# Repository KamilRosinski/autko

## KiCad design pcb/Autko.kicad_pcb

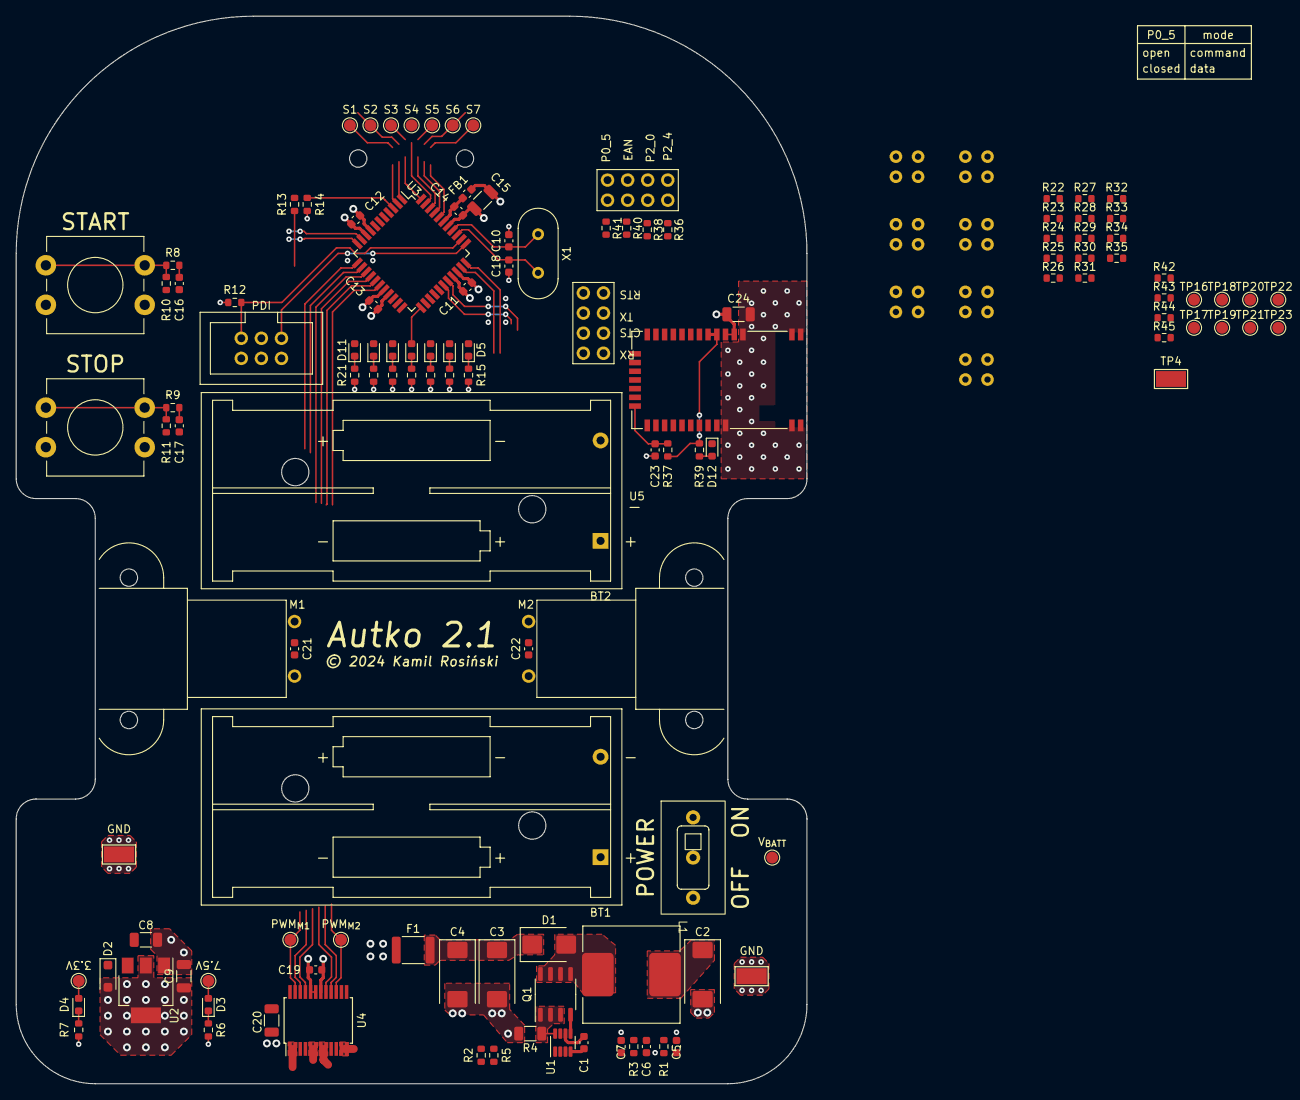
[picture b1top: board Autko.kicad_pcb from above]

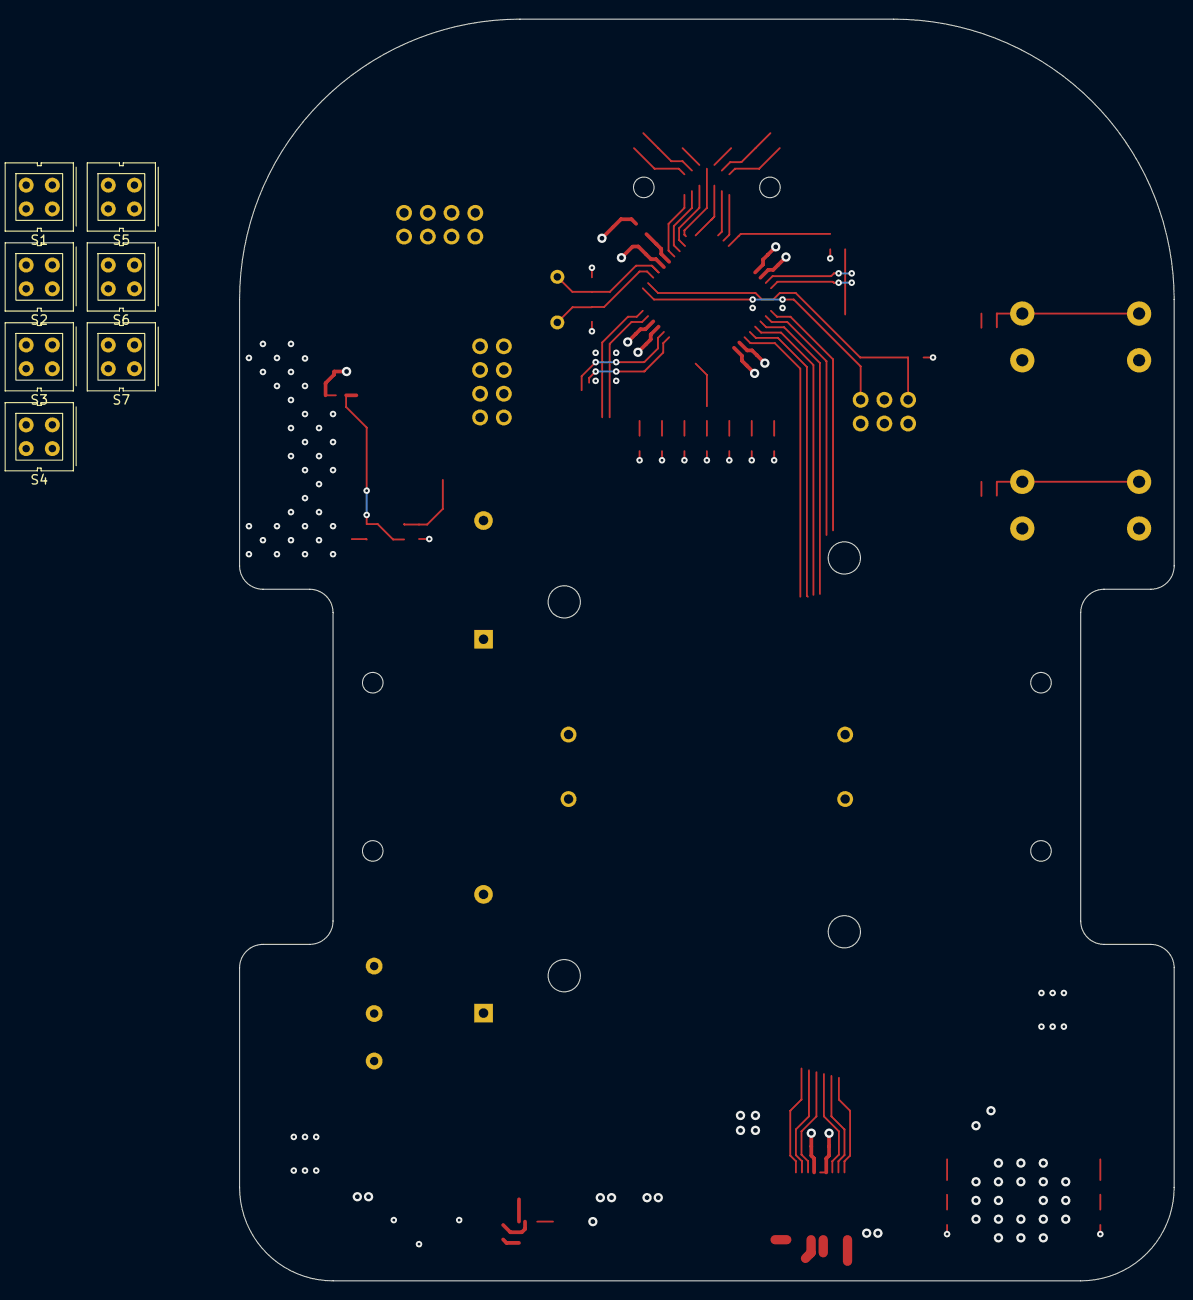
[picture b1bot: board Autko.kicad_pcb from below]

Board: 4 copper layers, 100.0 x 135.0 mm, 131 parts (7 on the bottom side), 88 nets.

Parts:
BT1, BT2: 2xAAA; BatteryHolder_Keystone_2468_2xAAA
C1, C5, C11, C12, C13, C14, C16, C17, C19, C21, C22, C23: 100nF; C_0603_1608Metric
C2: 47uF; CP_EIA-7343-20_Kemet-V
C3, C4: 33uF; CP_EIA-7343-20_Kemet-V
C6: 2.2nF; C_0603_1608Metric
C7: 100pF; C_0603_1608Metric
C8: 1uF; C_1206_3216Metric
C9, C15, C20, C24: 10uF; C_1206_3216Metric
C10, C18: 30pF; C_0603_1608Metric
D1: SL52-3G; D_SMB
D2: SL1A; D_SOD-123F
D3, D4: GREEN; LED_0603_1608Metric
D5, D6, D7, D8, D9, D10, D11: ORANGE; LED_0603_1608Metric
D12: BLUE; LED_0603_1608Metric
F1: 2A; Fuse_1812_4532Metric
FB1: 220R; C_0603_1608Metric
J1: PDI; IDC-Header_2x03_P2.54mm_Vertical
JP1, JP2: Jumper_x4_Bridged; PinHeader_2x04_P2.54mm_Vertical
L1: 3.3uH; Coilcraft_MSS1260
M1: LEFT; Pololu_DC_micro
M2: RIGHT; Pololu_DC_micro
Q1: SO-8_3.9x4.9mm_P1.27mm
R1: 1MR; R_0603_1608Metric
R2: 53.6kR; R_0603_1608Metric
R3: 18kR; R_0603_1608Metric
R4: 20mR; R_1206_3216Metric
R5: 10.2kR; R_0603_1608Metric
R6: 5.1kR; R_0603_1608Metric
R7: 820R; R_0603_1608Metric
R8, R9, R12, R13, R14, R37: 10kR; R_0603_1608Metric
R10, R11, R42, R43, R44, R45: 1kR; R_0603_1608Metric
R15, R16, R17, R18, R19, R20, R21: 680R; R_0603_1608Metric
R22, R24, R26, R28, R30, R32, R34: 640R; R_0603_1608Metric
R23, R25, R27, R29, R31, R33, R35: 20kR; R_0603_1608Metric
R36, R38, R39, R40, R41: 100R; R_0603_1608Metric
S1, S2, S3, S4, S5, S6, S7: CNY70; Vishay_CNY70
SW1: POWER; Knitter-Switch_MSS_3112_D
SW2: START; 12mm_tact_switch
SW3: STOP; 12mm_tact_switch
TP1, TP2, TP6, TP7, TP8, TP9, TP10, TP11, TP12, TP13, TP14, TP15, TP16, TP17, TP18, TP19, TP20, TP21, TP22, TP23: TestPoint; TestPoint_Pad_D1.5mm
TP3, TP4, TP5: TestPoint; TestPoint_Keystone_5019_Minature
U1: LTC3872; SOT-23-8
U2: TLV761; SOT-223-3_TabPin2
U3: ATxmega16A4U-A; TQFP-44_10x10mm_P0.8mm
U4: TB6612FNG; SSOP-24_5.3x8.2mm_P0.65mm
U5: RN4678
X1: 8MHz; Crystal_HC49-4H_Vertical

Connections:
+3.3V: C9.1, C11.1, C12.1, C13.1, C15.1, C19.1, C24.1, D2.2 (A), D4.2 (A), FB1.2, J1.2, R12.1, S1.3 (C), S2.3 (C), S3.3 (C), S4.3 (C), S5.3 (C), S6.3 (C), S7.3 (C), SW2.2, SW3.2, TP6.1, U2.2 (VO), U3.9 (VCC), U3.19 (VCC), U3.31 (VCC), U4.19 (STBY), U4.20 (VCC), U5.4 (BAT_IN), U5.5 (SW_BTN)
+7.5V: C8.1, C20.1, D2.1 (K), D3.2 (A), F1.2, S1.1 (A), S2.1 (A), S3.1 (A), S4.1 (A), S5.1 (A), S6.1 (A), S7.1 (A), TP2.1, U2.3 (VI), U4.13 (VM2), U4.14 (VM3), U4.24 (VM1)
+BATT: C1.1, C2.1, L1.1, R1.1, R13.1, SW1.1 (A), TP1.1, U1.6 (VIN)
/Bluetooth/BT_3V3: JP1.1, R37.1, R39.2, U5.6 (LDO33_O), U5.7 (VDD_IO)
/Bluetooth/CTS: JP2.8, U3.29 (PE1)
/Bluetooth/EAN: R36.2, TP16.1, U5.20 (EAN)
/Bluetooth/P0_5: R41.2, TP19.1, U5.16 (P0_5)
/Bluetooth/P2_0: R40.2, TP18.1, U5.18 (P2_0)
/Bluetooth/P2_4: R38.2, TP17.1, U5.19 (P2_4)
/Bluetooth/RTS: JP2.6, U3.28 (PE0)
/Bluetooth/RX: JP2.4, U3.33 (PE3)
/Bluetooth/TX: JP2.2, U3.32 (PE2)
/Bluetooth/~RST: C23.1, R37.2, U5.21 (~RST)
/Line sensors/SENSOR1: R23.1, S1.4 (E), TP7.1, U3.2 (PA6)
/Line sensors/SENSOR2: R25.1, S2.4 (E), TP8.1, U3.1 (PA5)
/Line sensors/SENSOR3: R27.1, S3.4 (E), TP9.1, U3.44 (PA4)
/Line sensors/SENSOR4: R29.1, S4.4 (E), TP10.1, U3.43 (PA3)
/Line sensors/SENSOR5: R31.1, S5.4 (E), TP11.1, U3.42 (PA2)
/Line sensors/SENSOR6: R33.1, S6.4 (E), TP12.1, U3.41 (PA1)
/Line sensors/SENSOR7: R35.1, S7.4 (E), TP13.1, U3.40 (AREFA/PA0)
/Microcontroller/BTN_START: C16.1, R8.1, U3.10 (PC0)
/Microcontroller/BTN_STOP: C17.1, R9.1, U3.11 (PC1)
/Microcontroller/LED1: D5.2 (A), U3.26 (PD6)
/Microcontroller/LED2: D6.2 (A), U3.25 (PD5)
/Microcontroller/LED3: D7.2 (A), U3.24 (PD4)
/Microcontroller/LED4: D8.2 (A), U3.23 (PD3)
/Microcontroller/LED5: D9.2 (A), U3.22 (PD2)
/Microcontroller/LED6: D10.2 (A), U3.21 (PD1)
/Microcontroller/LED7: D11.2 (A), U3.20 (PD0)
/Microcontroller/M1_IN1: U3.14 (PC4), U4.21 (AIN1)
/Microcontroller/M1_IN2: U3.13 (PC3), U4.22 (AIN2)
/Microcontroller/M1_PWM: TP14.1, U3.12 (PC2), U4.23 (PWMA)
/Microcontroller/M2_IN1: U3.15 (PC5), U4.17 (BIN1)
/Microcontroller/M2_IN2: U3.16 (PC6), U4.16 (BIN2)
/Microcontroller/M2_PWM: TP15.1, U3.17 (PC7), U4.15 (PWMB)
/Microcontroller/PDI_CLK: J1.5, R12.2, U3.35 (~RESET/PDI_CLK)
/Microcontroller/PDI_DATA: J1.1, U3.34 (PDI_DATA)
/Microcontroller/XTAL1: C10.1, U3.37 (PR1/XTAL1), X1.2
/Microcontroller/XTAL2: C18.1, U3.36 (PR0/XTAL2), X1.1
GND: BT2.2 (-), C1.2, C2.2, C3.2, C4.2, C5.2, C6.2, C7.2, C8.2, C9.2, C10.2, C11.2, C12.2, C13.2, C14.2, C15.2, C16.2, C17.2, C18.2, C19.2, C20.2, C23.2, C24.2, J1.6, JP1.3, JP1.5, JP1.7, R4.2, R5.2, R6.2, R7.2, R10.2, R11.2, R14.2, R15.2, R16.2, R17.2, R18.2, R19.2, R20.2, R21.2, R22.2, R23.2, R24.2, R25.2, R26.2, R27.2, R28.2, R29.2, R30.2, R31.2, R32.2, R33.2, R34.2, R35.2, TP3.1, TP4.1, TP5.1, U1.1 (IPRG), U1.4 (GND), U2.1 (GND), U3.8 (GND), U3.18 (GND), U3.30 (GND), U3.38 (GND), U4.3 (PGND1), U4.4 (PGND1), U4.9 (PGND2), U4.10 (PGND2), U4.18 (GND), U5.1 (GND), U5.2 (GND), U5.3 (GND), U5.31 (GND), U5.32 (GND), U5.33 (GND)
unnamed: BT1.1 (+), SW1.2 (B)
unnamed: BT1.2 (-), BT2.1 (+)
unnamed: C6.1, R3.1
unnamed: D1.2 (A), L1.2, Q1.5 (D), Q1.6 (D), Q1.7 (D), Q1.8 (D)
unnamed: C3.1, C4.1, D1.1 (K), F1.1, R2.1
unnamed: D3.1 (K), R6.1
unnamed: D4.1 (K), R7.1
unnamed: D5.1 (K), R15.1
unnamed: D6.1 (K), R16.1
unnamed: D7.1 (K), R17.1
unnamed: D8.1 (K), R18.1
unnamed: D9.1 (K), R19.1
unnamed: D10.1 (K), R20.1
unnamed: D11.1 (K), R21.1
unnamed: D12.2 (A), R39.1
unnamed: D12.1 (K), U5.30 (LED)
unnamed: JP1.2, R36.1
unnamed: JP1.4, R38.1
unnamed: JP1.6, R40.1
unnamed: JP1.8, R41.1
unnamed: JP2.1, R42.2
unnamed: JP2.3, R43.2
unnamed: JP2.5, R44.2
unnamed: JP2.7, R45.2
unnamed: C21.1, M1.1 (+), U4.1 (AO1), U4.2 (AO1)
unnamed: C21.2, M1.2 (-), U4.5 (AO2), U4.6 (AO2)
unnamed: C22.1, M2.2 (+), U4.11 (BO1), U4.12 (BO1)
unnamed: C22.2, M2.1 (-), U4.7 (BO2), U4.8 (BO2)
unnamed: Q1.4 (G), U1.5 (NGATE)
unnamed: R8.2, R10.1, SW2.1
unnamed: R9.2, R11.1, SW3.1
unnamed: R22.1, S1.2 (K)
unnamed: R24.1, S2.2 (K)
unnamed: R26.1, S3.2 (K)
unnamed: R28.1, S4.2 (K)
unnamed: R30.1, S5.2 (K)
unnamed: R32.1, S6.2 (K)
unnamed: R34.1, S7.2 (K)
unnamed: R2.2, R5.1, U1.3 (FB)
unnamed: C7.1, R3.2, U1.2 (ITH)
unnamed: C5.1, R1.2, U1.7 (RUN/SS)
unnamed: Q1.1 (S), Q1.2 (S), Q1.3 (S), R4.1, U1.8 (SW)
unnamed: C14.1, FB1.1, U3.39 (AVCC)
unnamed: R13.2, R14.1, U3.3 (PA7)
unnamed: R44.1, TP22.1, U5.17 (P0_0/RTS)
unnamed: R45.1, TP23.1, U5.15 (P1_7/CTS)
unnamed: R43.1, TP21.1, U5.22 (UART_RX)
unnamed: R42.1, TP20.1, U5.23 (UART_TX)

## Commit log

2023-04-02 Initial commit - empty project
2023-04-02 Add .gitignore
2023-04-02 Hierarchical sheets
2023-04-03 .gitignore update
2023-04-03 Created LTC3872 symbol
2023-04-03 Power supply initial schematic
2023-04-05 Created Si4368DY symbol
2023-04-05 Power supply voltage regulators
2023-04-05 Power supply schematic beautified
2023-04-05 Initial microcontroller schematic
2023-04-06 Uppercase project name
2023-04-06 Microcontroller schematic
2023-04-07 Motors schematic
2023-04-09 Ferrite bead added to uC AVCC pin
2023-04-09 10uF removed from uC power supply
2023-04-12 Created RN4870 symbol
2023-04-26 Line sensors
2023-04-26 Bluetooth initial schematic
2023-04-30 Bluetooth schematic
2023-05-02 Annotate schematics
2023-05-02 ERC fixes
2023-05-08 Move KiCad project to dedicated folder
2023-05-08 Android app initial commit
2023-05-08 Microcontroller initial commit
2023-05-09 Application code refactored to use data binding and ViewModel
2023-05-11 Added RN4678 symbol & footprint
2023-05-14 Pololu micro DC motor footprint added
2023-05-14 Pololu ball caster footprint added
2023-05-14 Battery holder footprint added
2023-05-14 Bluetooth RN4870 replaced with RN4678
2023-05-14 Schematic annotated
2023-05-31 [pcb] Test point added
2023-06-04 [pcb] Schematic clean-up
2023-06-05 [pcb] Footprints assigned
2023-06-05 [app] Ability to turn Bluetooth on
2023-06-05 [pcb] Missing connection
2023-06-07 [app] BT permissions handling
2023-06-08 [pcb] Add 100R resistor for BT status LED
2023-06-16 [app] BT scan added
2023-06-16 [app] Remove unused code
2023-06-25 [app] BtScanDialogFragment added
2023-06-25 [app] Code clean-up
2023-07-07 [app] Bugfixes on BT devices list
2023-07-23 [app] BT Service
2023-07-30 [app] BT connection works
2023-09-19 [pcb] Rework schematic for ATxmega16A4U
2023-09-21 Power switch footprint and initial pcb
2023-09-21 [pcb] Power switch footprint assigned
2023-09-21 [pcb] Motor footprint fix
2023-09-23 [pcb] Initial layout
2023-09-30 [pcb] Line sensors placed
2023-10-02 [pcb] Trying to minimize number of vias
2023-10-05 [pcb] Route PDI and UART
2023-10-05 [pcb] Rotate uC by 45 deg
2023-10-06 [pcb] Remove unnecessary capacitors
2023-10-07 [pcb] Replace 5V with 3.3V
2023-10-10 [pcb] BT routing
2023-10-10 [pcb] Ball caster added to PCB
2023-10-21 [pcb] Line sensors routed
2023-10-21 [pcb] Buttons routed
2023-10-30 [pcb] Boost converter routing
2023-11-01 [pcb] Voltage regulator and motor driver
2023-11-01 [pcb] Bluetooth ground plane
2023-11-11 [pcb] Some power routing
2023-11-15 [pcb] Alternative power routing
2023-12-27 [pcb] 4 layer PCB
2023-12-28 [pcb] BT config rework
2023-12-29 [pcb] Almost ready
2023-12-31 [pcb] Final touches
2024-01-14 [pcb] More final touches, UART test ponts added.
2024-01-14 [pcb] Mark high-precision resistors
2024-01-14 [pcb] 10uF capacitor changed from A to T package
2024-01-21 [pcb] ERC/DRC checks
2024-01-21 [pcb] BOM added
2024-01-21 [pcb] ERC fixes
2024-01-23 [pcb] Swap voltage divider resistors
2024-01-25 [pcb] Fix typos in boost converter calculations
2024-01-27 [pcb] Change Schottky diode
2024-01-27 [pcb] Inductor upgrade, boost converter clean-up
2024-01-28 [pcb] Line sensors changed to pull-down and re-routed
2024-01-28 [pcb] Max voltage label added
2024-01-28 [pcb] Move label
2024-01-29 [pcb] Motors resized to 24mm
2024-02-03 [pcb] Voltage regulator changed to TLV761
2024-02-03 [pcb] Add missing vias, fix power traces
2024-02-25 [pcb] Test points reduced to 1.5mm; flow control series resistors added
2024-02-25 [pcb] Rename line sensors to S1..S7
2024-02-25 [pcb] Fix power plane edge
2024-03-12 [bt] Configuration commands
2024-03-16 [bt] Configuration commands updated
2024-03-17 [pcb] Bluetooth configuration simplified
2024-03-23 [pcb] Assign smaller footprints
2024-03-24 [pcb] Start reworking pcb with 0603 components
2024-03-24 [bt] Disable BT status strings
2024-03-24 [pcb] Batteries split into 2 holders
2024-03-26 [pcb] Routing on smaller board. Before removal of button.

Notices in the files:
pcb/Autko.kicad_pcb:
© 2024 Kamil Rosiński
